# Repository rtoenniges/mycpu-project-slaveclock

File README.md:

# MyCPU_PRO_SCC
An extension for the [MyCPU](http://www.mycpu.eu/) from Dennis Kuschel to get the timesignal DCF77 and control a slave clock (https://en.wikipedia.org/wiki/Slave_clock)

## Hardware
- External module (Basic board)
- Rack extension (Clock control & DCF77 signal converting)

## Software
- scc.asm (Main program)
- sl60dcf77.asm (Library for DCF77 decoding (Can be found at https://github.com/rtoenniges/MyCPU_LIB_DCF77))

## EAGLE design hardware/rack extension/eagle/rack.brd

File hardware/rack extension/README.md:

# MyCPU_PRG_SCC
## Rack extension

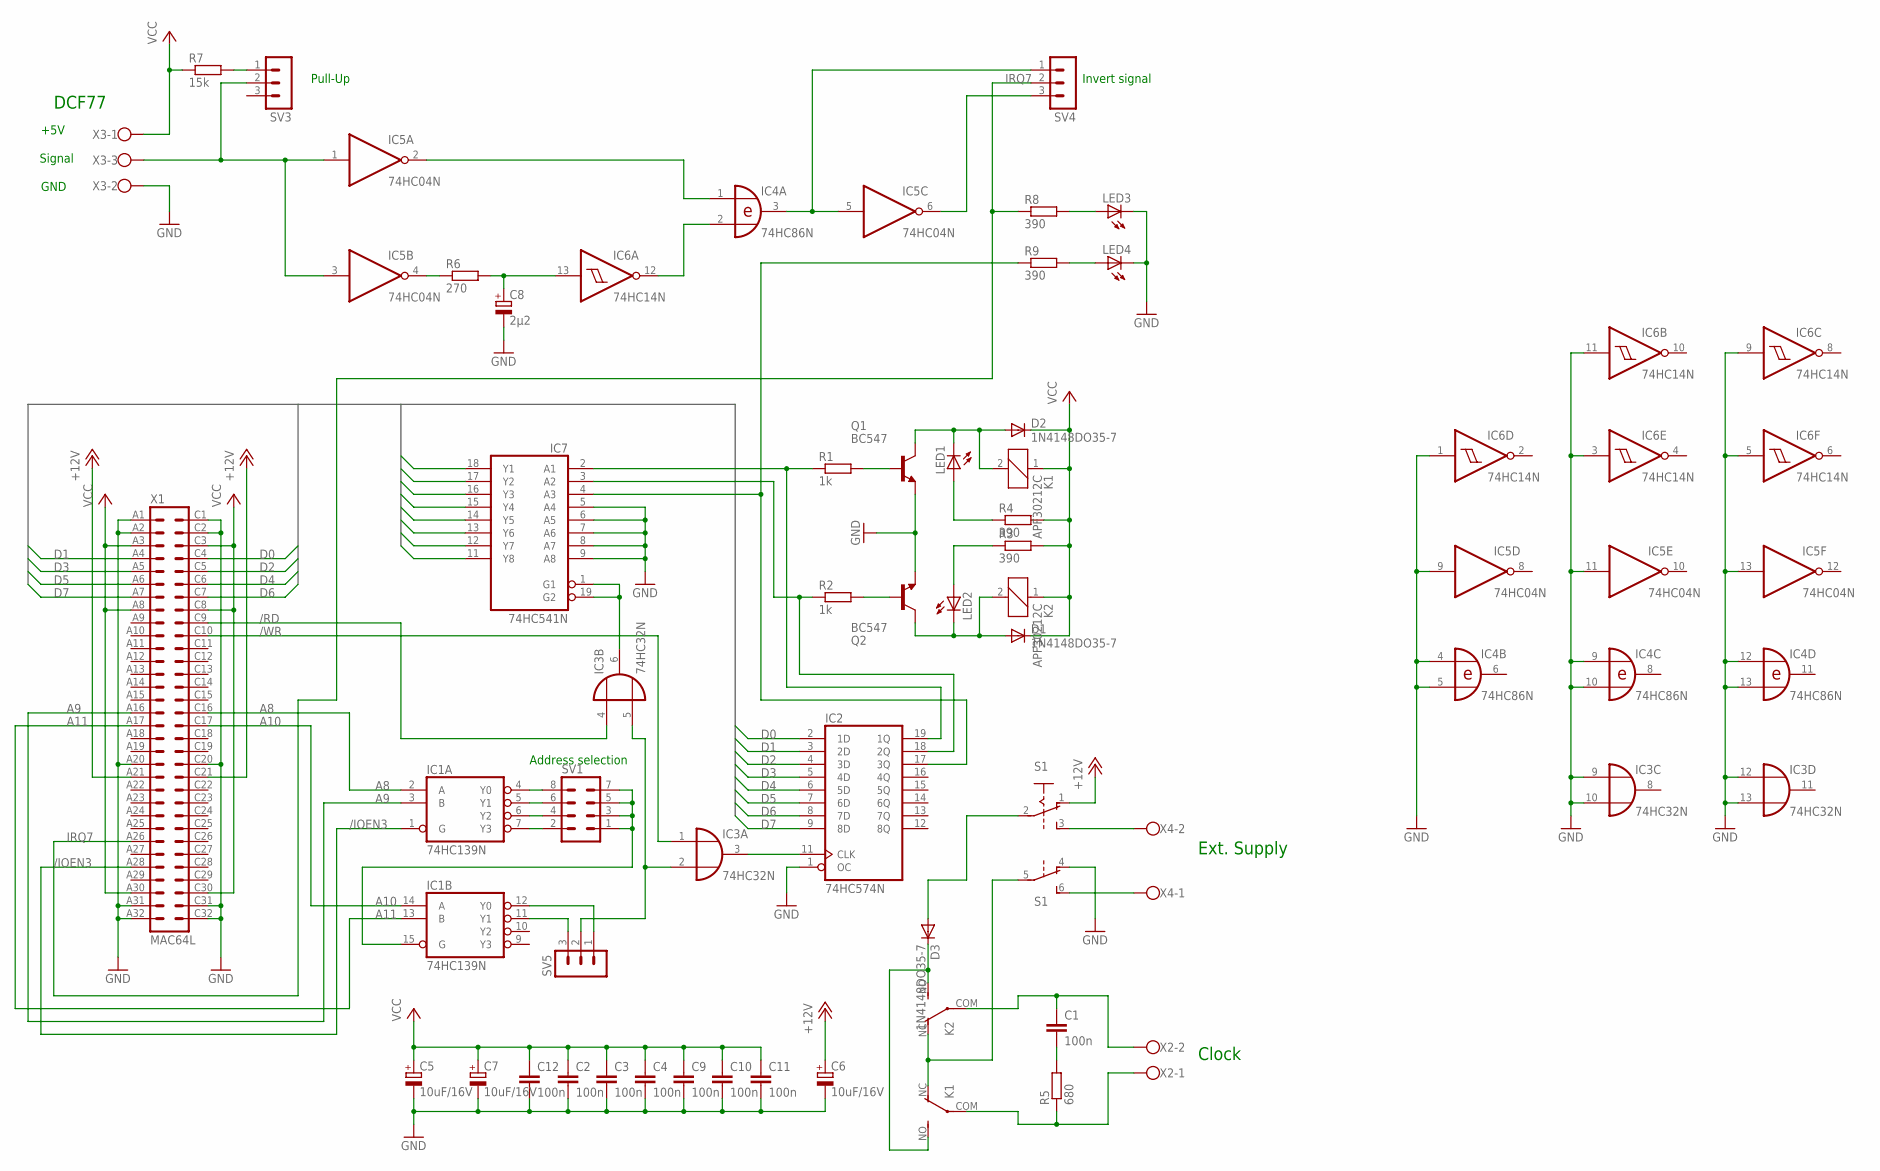
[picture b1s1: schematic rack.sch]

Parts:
C1, C2, C3, C4, C9, C10, C11, C12: 100n; C050-024X044
C5, C6, C7: 10uF/16V; TT2D5
C8: 2µ2; E2,5-6E
D1, D2, D3: 1N4148DO35-7; DO35-7
IC1: 74HC139N; DIL16
IC2: 74HC574N; DIL20
IC3: 74HC32N; DIL14
IC4: 74HC86N; DIL14
IC5: 74HC04N; DIL14
IC6: 74HC14N; DIL14
IC7: 74HC541N; DIL20
K1, K2: APF30212C
LED1, LED2, LED3, LED4: LEDB155; Q62902-B155
Q1, Q2: BC547; TO92
R1, R2: 1k; 0204/7
R3, R4, R8, R9: 390; 0204/7
R5: 680; 0204/7
R6: 270; 0204/7
R7: 15k; 0204/7
S1: A68-A31
SV1: MA04-2
SV3, SV4, SV5: MA03-1
X1: MAC64L
X2, X4: W237-102
X3: W237-103

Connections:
+12V: C6.+, S1.1 (O), X1.A21, X1.C21
/IOEN3: IC1.1 (G), X1.A28
/RD: IC3.4 (I0), X1.C9
/WR: IC3.1 (I0), X1.C10
A8: IC1.2 (A), X1.C16
A9: IC1.3 (B), X1.A16
A10: IC1.14 (A), X1.C17
A11: IC1.13 (B), X1.A17
D0: IC2.2 (1D), IC7.18 (Y1), X1.C4
D1: IC2.3 (2D), IC7.17 (Y2), X1.A4
D2: IC2.4 (3D), IC7.16 (Y3), X1.C5
D3: IC2.5 (4D), IC7.15 (Y4), X1.A5
D4: IC2.6 (5D), IC7.14 (Y5), X1.C6
D5: IC2.7 (6D), IC7.13 (Y6), X1.A6
D6: IC2.8 (7D), IC7.12 (Y7), X1.C7
D7: IC2.9 (8D), IC7.11 (Y8), X1.A7
GND: C2.2, C3.2, C4.2, C5.-, C6.-, C7.-, C8.-, C9.2, C10.2, C11.2, C12.2, IC1.8 (GND), IC2.1 (OC), IC2.10 (GND), IC3.7 (GND), IC3.9 (I0), IC3.10 (I1), IC3.12 (I0), IC3.13 (I1), IC4.4 (I0), IC4.5 (I1), IC4.7 (GND), IC4.9 (I0), IC4.10 (I1), IC4.12 (I0), IC4.13 (I1), IC5.7 (GND), IC5.9 (I), IC5.11 (I), IC5.13 (I), IC6.1 (I), IC6.3 (I), IC6.5 (I), IC6.7 (GND), IC6.9 (I), IC6.11 (I), IC7.5 (A4), IC7.6 (A5), IC7.7 (A6), IC7.8 (A7), IC7.9 (A8), IC7.10 (GND), LED3.K (C), LED4.K (C), Q1.1 (E), Q2.1 (E), S1.4 (O), X1.A1, X1.A2, X1.A20, X1.A31, X1.A32, X1.C1, X1.C2, X1.C20, X1.C31, X1.C32, X3.2
IRQ7: R8.1, SV4.2, X1.A26
unnamed: IC1.4 (Y0), SV1.8
unnamed: IC1.5 (Y1), SV1.6
unnamed: IC1.6 (Y2), SV1.4
unnamed: IC1.7 (Y3), SV1.2
unnamed: IC2.17 (3Q), IC7.4 (A3), R9.1
unnamed: IC1.11 (Y1), SV5.3
unnamed: IC1.12 (Y0), SV5.1
unnamed: IC1.15 (G), SV1.1, SV1.3, SV1.5, SV1.7
unnamed: IC2.11 (CLK), IC3.3 (O)
unnamed: Q1.2 (B), R1.2
unnamed: IC2.19 (1Q), IC7.2 (A1), R1.1
unnamed: IC2.18 (2Q), IC7.3 (A2), R2.1
unnamed: Q2.2 (B), R2.2
unnamed: D2.A, K1.2, LED1.K (C), Q1.3 (C)
unnamed: C1.2, R5.2
unnamed: D1.A, K2.2, LED2.K (C), Q2.3 (C)
unnamed: C1.1, K2.COM, X2.2
unnamed: LED1.A, R4.1
unnamed: LED2.A, R3.1
unnamed: K1.COM, R5.1, X2.1
unnamed: D3.C, K1.NO (S), K2.NO (S)
unnamed: IC5.4 (O), R6.1
unnamed: C8.+, IC6.13 (I), R6.2
unnamed: IC4.1 (I0), IC5.2 (O)
unnamed: IC4.2 (I1), IC6.12 (O)
unnamed: IC4.3 (O), IC5.5 (I), SV4.1
unnamed: K1.NC (O), K2.NC (O), S1.5
unnamed: R7.2, SV3.1
unnamed: IC5.1 (I), IC5.3 (I), SV3.2, X3.3
unnamed: IC5.6 (O), SV4.3
unnamed: LED3.A, R8.2
unnamed: S1.3 (S), X4.2
unnamed: S1.6 (S), X4.1
unnamed: D3.A, S1.2
unnamed: IC3.6 (O), IC7.1 (G1), IC7.19 (G2)
unnamed: IC3.2 (I1), IC3.5 (I1), SV5.2
unnamed: LED4.A, R9.2
VCC: C2.1, C3.1, C4.1, C5.+, C7.+, C9.1, C10.1, C11.1, C12.1, D1.C, D2.C, IC1.16 (VCC), IC2.20 (VCC), IC3.14 (VCC), IC4.14 (VCC), IC5.14 (VCC), IC6.14 (VCC), IC7.20 (VCC), K1.1, K2.1, R3.2, R4.2, R7.1, X1.A3, X1.A8, X1.A30, X1.C3, X1.C8, X1.C30, X3.1

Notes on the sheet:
Address selection
DCF77
+5V
GND
Signal
Clock
Pull-Up
Ext. Supply
Invert signal

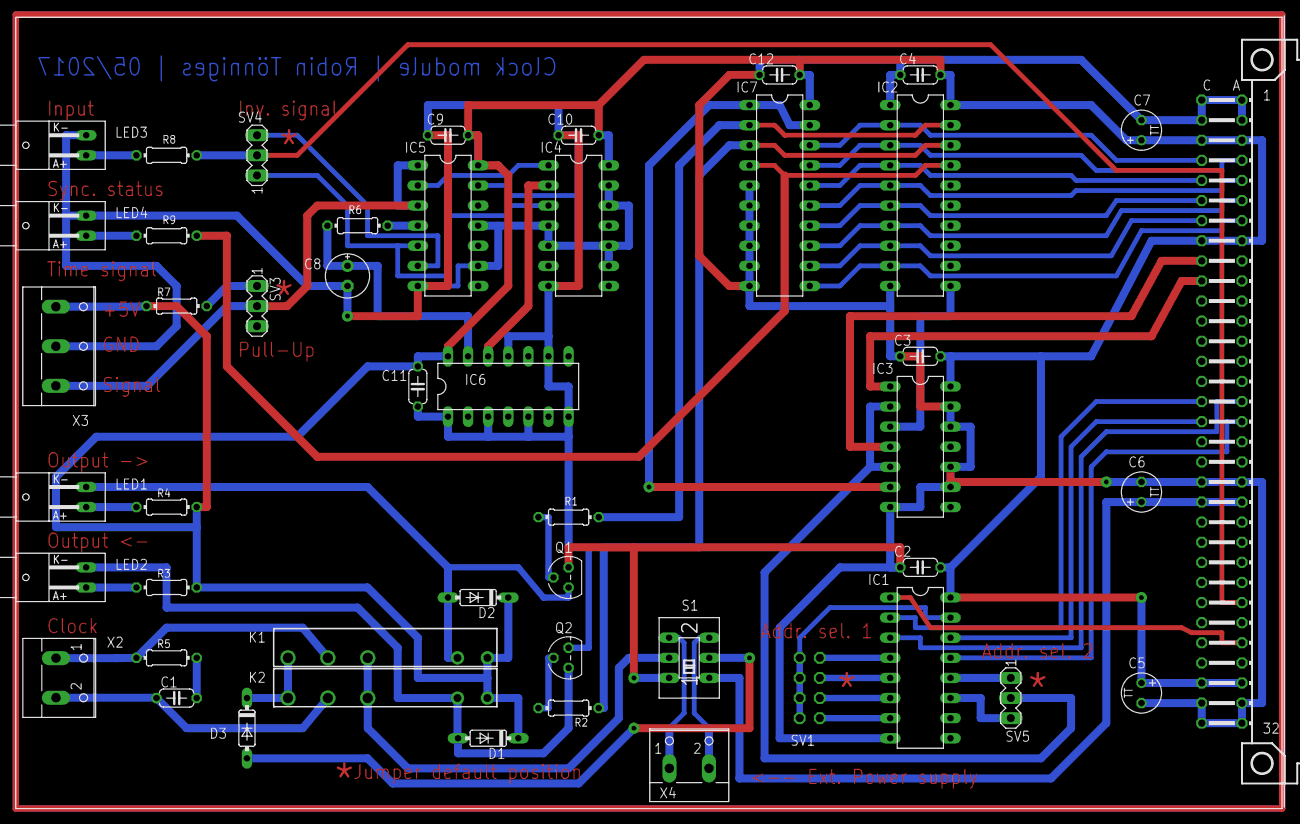
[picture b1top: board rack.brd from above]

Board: 2 copper layers, 160.3 x 100.2 mm, 48 parts (1 on the bottom side), 56 nets.

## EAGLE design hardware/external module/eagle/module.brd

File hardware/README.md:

# Hardware
## External module (Basic board without DCF77-Input)
This board only generates the alternating current to drive the clock.

## Rack Extension (DCF77-Input and slave-clock control)
This board is connected directly to the MyCPU-Backplane Bus.
It provides support to connect a DCF77-Receiver and generates the alternating
current to drive the clock.
Also it displays the status of the time synchronization and the active clock output.

**If you use this board and you have set the adress jumpers to the default position, you
have to change the "OUTPUT" declaration in "scc.asm" to '3500h'!**

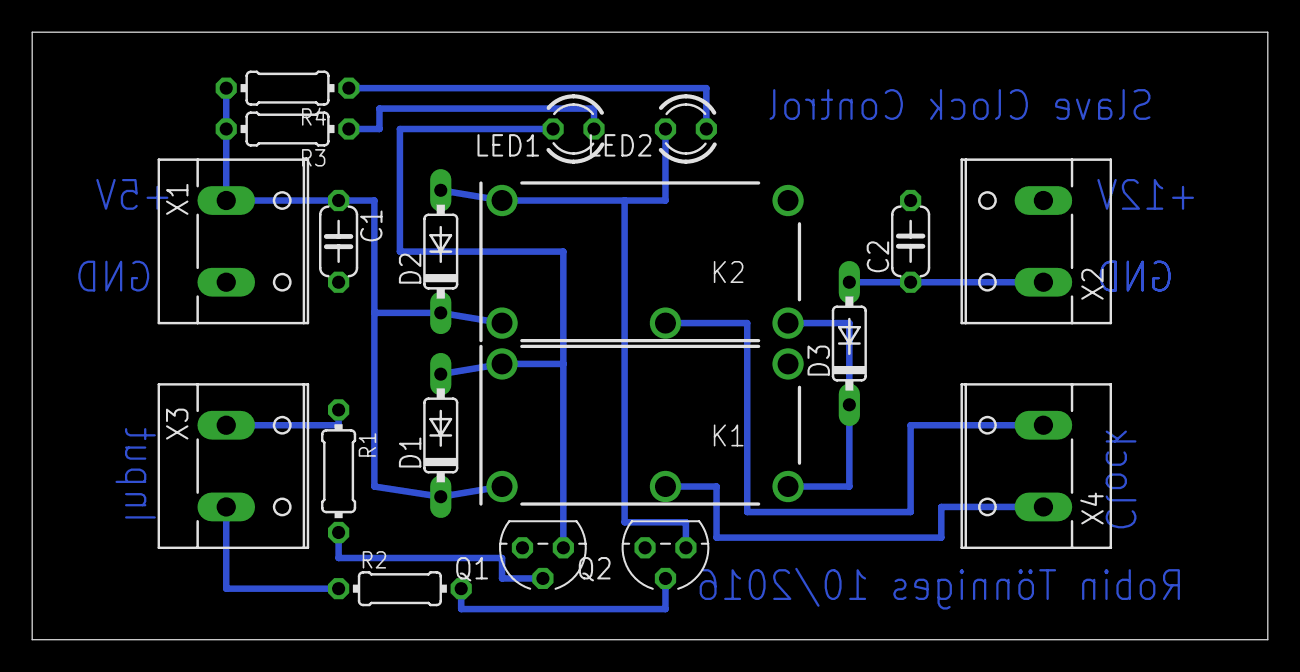
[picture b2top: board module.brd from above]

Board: 2 copper layers, 76.8 x 37.8 mm, 19 parts (0 on the bottom side), 14 nets.

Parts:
C1, C2: C050-024X044
D1, D2, D3: 1N4148DO35-7; DO35-7
K1, K2: PE005; PE
LED1, LED2: LED3MM
Q1, Q2: BC547; TO92
R1, R2, R3, R4: 0204/7
X1, X2, X3, X4: W237-132

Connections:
GND: C1.2, C2.2, K1.12, K2.12, Q1.1, Q2.1, X1.2, X2.2
unnamed: C2.1, D3.A, X2.1
unnamed: R1.1, X3.1
unnamed: K1.11, X4.1
unnamed: R2.1, X3.2
unnamed: K2.11, X4.2
unnamed: Q1.2, R1.2
unnamed: D1.A, K1.A2, LED1.K, Q1.3
unnamed: D2.A, K2.A2, LED2.K, Q2.3
unnamed: C1.1, D1.C, D2.C, K1.A1, K2.A1, R3.2, R4.2, X1.1
unnamed: LED1.A, R3.1
unnamed: Q2.2, R2.2
unnamed: D3.C, K1.14, K2.14
unnamed: LED2.A, R4.1

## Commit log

2016-10-24 First release
2016-10-29 New Hardware
2016-10-30 Update for new hardware
2016-11-10 Bad fail in rack hardware
    The switch S1 was connected wrong so the change from internal to
    external supply didnt work.
2016-11-10 Switched 74AC parts to 74HC
2017-03-20 Added licence
2017-04-06 Layout updated
    Updated layout from rack extension
2017-05-03 Litte changes in schematic and layout
    Added further description and fixed an naming issue in schmematic
2017-05-09 Value of PullUp from1k to 15k
2017-05-16 Little layout update
2017-05-31 Termination routine changed
    Clock outputs will now set to zero on termination
2024-09-01 Update scc.asm
    Changed to new sl60dcf77
2024-09-01 Create d
2025-12-30 Fix formatting in README.md for clarity
    Removed unnecessary underscores from the text.
